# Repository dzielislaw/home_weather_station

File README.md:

# home-weather-station
## English
This home weather station is a STM32 microcontroller-based device. It performs measurements such as:
 - indor temperature
 - outdoor temperature via external wired probe
 - atmospheric pressure
 - air humidity
 - PM (Particulate Matter) concentration
and moreover it alarms of presence of flammable gases such as propane or buthane.

https://github.com/user-attachments/assets/9bdbaac8-06a2-42ca-afe4-3092634e5976

## Polski
Projekt domowej stacji pogody oparty o wykorzystanie mikrokontrolera STM32G491RE. Wykonuje pomiary takie jak:
- temperatura wewnętrzna
- temperatura zewnętrzna
- ciśnienie atmosferyczne
- wilgotność powietrza
- stężenie pyłu zawieszonego PM1, PM2,5 oraz PM10 (jakości powietrza).

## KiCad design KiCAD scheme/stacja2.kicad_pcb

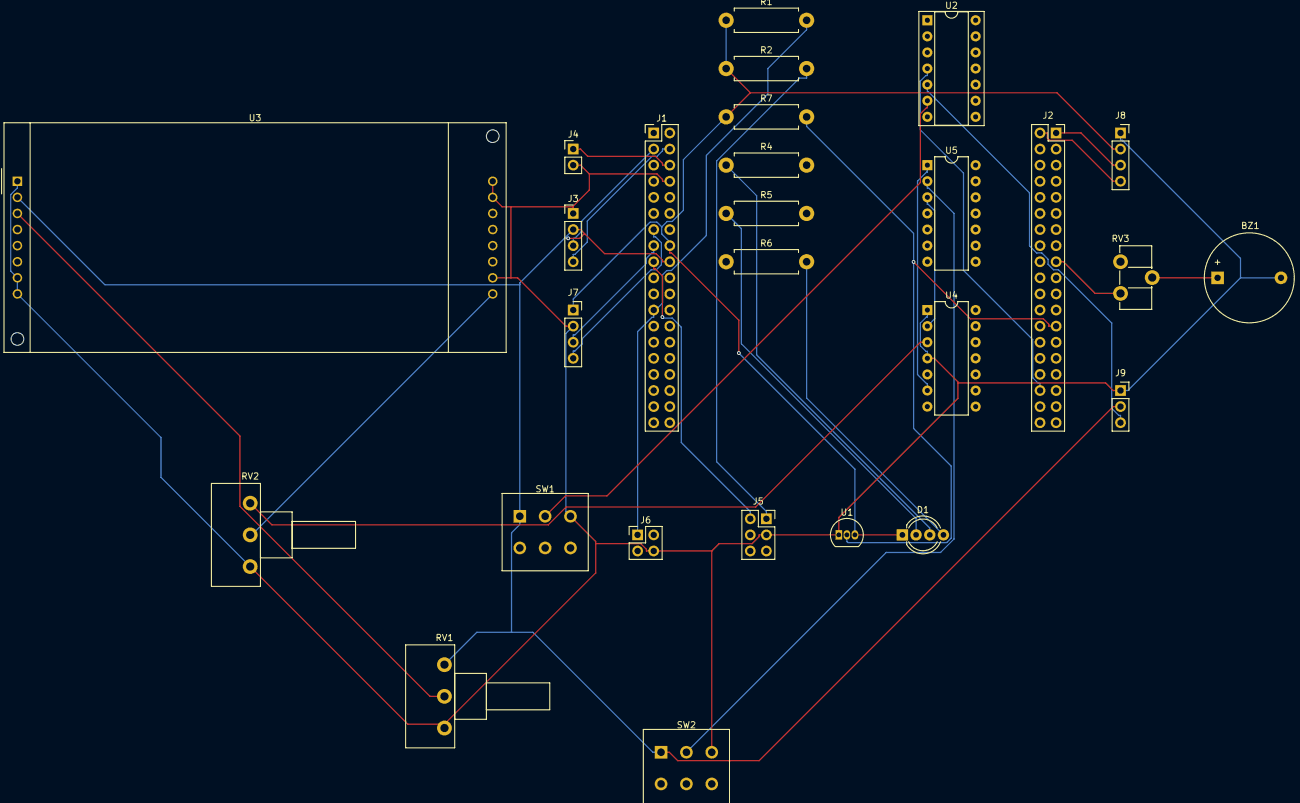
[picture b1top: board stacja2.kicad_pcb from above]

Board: 2 copper layers, 27 parts (0 on the bottom side), 36 nets.

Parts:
BZ1: Buzzer; Buzzer_D14mm_H7mm_P10mm
D1: DIODA_STATUSU; LED_D5.0mm-4_RGB_Wide_Pins
J1: ST_MORPHO_LEWA; PinHeader_2x19_P2.54mm_Vertical
J2: ST_MORPHO_PRAWA; PinSocket_2x19_P2.54mm_Vertical
J3: PMS7003; PinHeader_1x04_P2.54mm_Vertical
J4: złącze zasilania; PinHeader_1x02_P2.54mm_Vertical
J5: CELSIUS_FAHRENEIT_SWITCH; PinSocket_2x03_P2.54mm_Vertical
J6: RESET_TACT_SWITCH; PinHeader_2x02_P2.54mm_Vertical
J7: LPS25HB; PinSocket_1x04_P2.54mm_Vertical
J8: SHT35; PinSocket_1x04_P2.54mm_Vertical
J9: MQ-2; PinSocket_1x03_P2.54mm_Vertical
R1, R2: 47k; R_Axial_DIN0411_L9.9mm_D3.6mm_P12.70mm_Horizontal
R4, R5, R6: 460; R_Axial_DIN0411_L9.9mm_D3.6mm_P12.70mm_Horizontal
R7: 4k7; R_Axial_DIN0411_L9.9mm_D3.6mm_P12.70mm_Horizontal
RV1, RV2: 100k; Potentiometer_Piher_T-16H_Single_Horizontal
RV3: 200; Potentiometer_ACP_CA9-H5_Horizontal
SW1, SW2: SW_SPDT; SW_PUSH_E-Switch_FS5700DP_DPDT
U1: DS18B20; TO-92_Inline
U2: 4081; DIP-14_W7.62mm_Socket
U3: HD44780; NHD-0420H1Z
U4: 74AHCT125; DIP-14_W7.62mm
U5: 4071; DIP-14_W7.62mm

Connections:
3V3: D1.1 (A), J1.16, J7.4, J8.2, R1.1, R2.1, R7.1, U1.3 (V_{DD})
5V: J1.18, RV1.3, SW1.1 (A), SW2.1 (A), U3.2 (VDD)
+5V: J1.6, J4.1
BUZZER+: J2.14, RV3.3
C/F: J1.17, J5.2
GAS_TRIG: J2.34, U2.4
GND: BZ1.2 (-), J1.8, J3.1, J4.2, J5.3, J6.4, J7.3, J8.1, J9.1, RV1.1, RV2.1, SW1.3 (C), SW2.3 (C), U1.1 (GND), U3.1 (VSS), U3.5 (R/W), U3.7 (DB0), U3.8 (DB1), U3.9 (DB2), U3.10 (DB3), U3.15 (A), U4.1, U4.4
LCD_D4: J2.15, U3.11 (DB4)
LCD_D5: J2.17, U3.12 (DB5)
LCD_D6: J2.19, U3.13 (DB6)
LCD_D7: J2.21, U3.14 (DB7)
LCD_ENABLE: J2.11, U3.6 (E)
LCD_RS: J2.5, U3.4 (RS)
LED_ZIELONY: J1.28, R4.2
unnamed: BZ1.1 (+), RV3.2
unnamed: D1.4 (BK), R6.2
unnamed: D1.3 (GK), R4.1
unnamed: D1.2 (RK), R5.1
unnamed: J5.1, R2.2
unnamed: J9.3, U2.5
unnamed: RV2.3, U4.3
unnamed: SW1.2 (B), U2.6
unnamed: SW2.2 (B), U5.2
unnamed: RV2.2, U3.16 (K)
unnamed: RV1.2, U3.3 (VO)
unnamed: U4.2, U5.3
unnamed: U4.6, U5.1
ONE_WIRE: J2.25, R7.2, U1.2 (DQ)
PMS_RX: J1.3, J3.3
PMS_TX: J1.4, J3.4
RES_NRST: J1.23, J6.1, R1.2
SCL_1: J1.13, J7.1
SCL_2: J2.2, J8.4
SDA_1: J1.15, J7.2
SDA_2: J2.1, J8.3
VCC: J3.2, J9.2

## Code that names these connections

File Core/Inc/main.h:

/* USER CODE BEGIN Header */
/**
  ******************************************************************************
  * @file           : main.h
  * @brief          : Header for main.c file.
  *                   This file contains the common defines of the application.
  ******************************************************************************
  * @attention
  *
  * Copyright (c) 2024 STMicroelectronics.
  * All rights reserved.
  *
  * This software is licensed under terms that can be found in the LICENSE file
  * in the root directory of this software component.
  * If no LICENSE file comes with this software, it is provided AS-IS.
  *
  ******************************************************************************
  */
/* USER CODE END Header */

/* Define to prevent recursive inclusion -------------------------------------*/
#ifndef __MAIN_H
#define __MAIN_H

#ifdef __cplusplus
extern "C" {
#endif

/* Includes ------------------------------------------------------------------*/
#include "stm32g4xx_hal.h"

/* Private includes ----------------------------------------------------------*/
/* USER CODE BEGIN Includes */
#include "units.h"
/* USER CODE END Includes */

/* Exported types ------------------------------------------------------------*/
/* USER CODE BEGIN ET */
typedef struct
{
  float temp;
  float minTemp;
  float maxTemp;
  
  float outdoorTemp;
  float minOutdoorTemp;
  float maxOutdoorTemp;
  
  float pressure;
  float minPressure;
  float maxPressure;
  
  float humidity;
  float minHumidity;
  float maxHumidity;
  
  uint16_t pm1_0;
  uint16_t minPm1_0;
  uint16_t maxPm1_0;
  
  uint16_t pm2_5;
  uint16_t minPm2_5;
  uint16_t maxPm2_5;

  uint16_t pm10;
  uint16_t minPm10;
  uint16_t maxPm10;
  
  enum temperatureUnit tempUnit;
}Measurements;
/* USER CODE END ET */

/* Exported constants --------------------------------------------------------*/
/* USER CODE BEGIN EC */

/* USER CODE END EC */

/* Exported macro ------------------------------------------------------------*/
/* USER CODE BEGIN EM */

/* USER CODE END EM */

/* Exported functions prototypes ---------------------------------------------*/
void Error_Handler(void);

/* USER CODE BEGIN EFP */

/* USER CODE END EFP */

/* Private defines -----------------------------------------------------------*/
#define MAX_INPUT_Pin GPIO_PIN_14
#define MAX_INPUT_GPIO_Port GPIOC
#define MAX_INPU_Pin GPIO_PIN_15
#define MAX_INPU_GPIO_Port GPIOC
#define MIN_INPUT_Pin GPIO_PIN_4
#define MIN_INPUT_GPIO_Port GPIOA
#define LCD_ENABLE_Pin GPIO_PIN_5
#define LCD_ENABLE_GPIO_Port GPIOA
#define LCD_D4_Pin GPIO_PIN_7
#define LCD_D4_GPIO_Port GPIOA
#define LCD_D6_Pin GPIO_PIN_7
#define LCD_D6_GPIO_Port GPIOC
#define LCD_D7_Pin GPIO_PIN_9
#define LCD_D7_GPIO_Port GPIOA
#define LCD_BRIGHT_MAX_Pin GPIO_PIN_10
#define LCD_BRIGHT_MAX_GPIO_Port GPIOA
#define LCD_BRIGHT_NORM_Pin GPIO_PIN_12
#define LCD_BRIGHT_NORM_GPIO_Port GPIOA
#define TEMP_UNIT_INPUT_Pin GPIO_PIN_15
#define TEMP_UNIT_INPUT_GPIO_Port GPIOA
#define LCD_D5_Pin GPIO_PIN_6
#define LCD_D5_GPIO_Port GPIOB
#define MAKS_INPUT_Pin GPIO_PIN_7
#define MAKS_INPUT_GPIO_Port GPIOB
#define LCD_RS_Pin GPIO_PIN_9
#define LCD_RS_GPIO_Port GPIOB

/* USER CODE BEGIN Private defines */

/* USER CODE END Private defines */

#ifdef __cplusplus
}
#endif

#endif /* __MAIN_H */

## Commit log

2025-03-18 Program upload
2025-03-18 Added scheme preview
2025-04-01 Bugfix - video not displaying
2025-04-09 Added polish README
2025-04-09 bugfix
